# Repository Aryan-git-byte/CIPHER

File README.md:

# CIPHER — Journal Export

- Exported at: 2026-05-15T09:21:32Z
- Project ID: 8
- Entries: 12

## Entry 1
- ID: 206
- Author: TheMudGuy
- Created At: 2026-03-19T09:36:23Z

### Content

# CIPHER
## Compact Integrated Platform for Hardware Engineering and Research

### Objective:
An integrated portable workstation with 8 gigabytes of ram, plenty of storage (target - 256 gb ssd), Exposed GPIO headers(SPI, I2C, UART, etc) to test sensors, components directly. 
The communication protocols of the workstation are LTE, LoRa, WiFi, and BLE.
It will have the following ports:
- 4x USB 3.0 A port
- 1x USB-C for Charging
- 1x USB 3.0 C for Data
- 1x Ethernet Port
- 1x 3.5 mm Audio Jack
- 1x Barrel jack for backup power to power the workstation directly from wall adaptor.
- 1x SD card Slot
- 1x self bouncing Nano SIM card slot
- 1x HDMI port

**For the GPIO pins we will have:**
- GP0 - GP11 : Digital IO/ PWM/ ADC
- I2C(SDA, SCL)
- SPI (MOSI, MISO, SCK, CS)
- 2x 3V3 pin
- 2x GND pin
- 2x 5V pin

## Modularity:

The Cyberdeck will be divided into 1 main board and 5 daughterboards(this number can be changed as we develop further) that will communicate with each other using protocols such as SPI,UART etc.
The main board will have :
- The CM5108000module itself
- And all the ports

**Now the Daughterboards are:**
1. Power Board:
 - it is responsible to lookup for the battery
 - Charging
 - Powering all the components in CIPHER
 - and exposing power outlet on the panel too
 - charge the batteries
 - protect from overcharge & over discharge, implement cell balancing, and obv prevent it from blowing up
 - supply 2  channels of 5v at 6A peak current and 3.3v at 5A peak with low power loss & high efficiency
 - monitor batteries and report it to CM5
 -8 18650 cells @ 2600 mah

2. Instrument Board
 - This board will have the Logic analyzer and a oscilloscope
 - the main mcu of this board will be a Pi pico 2, it will be placed there through female socket, making it replacable
3. GPIO Board
 - This board is responsible to expose the GPIO pins out the laptop
 - The main MCU of this board will be a  Pi pico 2, it will be placed there through female socket, making it replacable
 - It will be programmable through USB, which will be routed inside of the CIPHER
4. Radio Board
 - This will have all the communication modules such as LoRa, LTE, Sim slot, Antenna conectors.
 - This board will be operateed directly by the Main Board
5. Keyboard & Trackpad
 - This board will have a low profile 60-75% keyboard(tbd)
 - and a trackpad
 - The main mcu of this board is a  Pi pico 1, it will also be placed there through female socket, making it replacable

also i m using the devboard instead of IC , cuz using devboard can make it replacable and not waste the whole thing just bcz of a mcu if it blow. and it can also save up SMT cost.
currently i have started working on the power board
here how it went 
firstly i checked some ustom cyberdeck by others and how they are powered, read datasheet of cm5 about how much power it needs to work reliably. then  i searched differnet batteries & cells avaialble , from which i chose 
https://robu.in/product/dmegc-inr18650-26e-3-7v-2600mah-li-ion-battery/#tab-product_download_66939_tab

read the datasheet of that exact batteries, searched reviews, studied abt it, then i started looking for things such as buck converter ics, charging ics, which were pretty hard to find in india so at last i decided to use LCSC.
then i read the datasheets of the following components to be used, and implemented their application in my schematic, and i also implemented battery protection features, and fuel gauge, 
this whole process was too long, from reading datasheets, searching hrs for a single ic to found that it has to be imported, now here are some pics of the schematics that i 've created as of now:

also, i forgot to timelapse this cm5 carrier board work, although its not much so i'll just ignore the hrs of it, it was smthg around 1-2 hrs too, it was mostly taken reefernce from the official cm5 carrier board thats why it was quick

### Recording Links

- https://public.lapse-hackclub.link/timelapses/pCE9Pr_62jN5/timelapse-pCE9Pr_62jN5.mp4

## Entry 2
- ID: 320
- Author: TheMudGuy
- Created At: 2026-03-22T14:30:19Z

### Content

today, first i started by implemting chargin feature in my schematic with ip2368, but i found out that the symbol of this ic didnt existed for kicad, so had to drew it too, and then started implementing it in the board , and overall completed the whole power board except the connectors that are to be placed:

after that i started working on the navigation board which had, a tft, an oled, low profile mx style switches, rotary encoders and a touch panel for trackpad.

the problem that i faced while making the navigation board was that i couldnt find a easy to use modular trackpad or touchpad at first, which i overcame by using this touch panel for evelta:

after that i started working on the breakout board which is still kinda incomplete, i spent most of my time finding the best ICs for integrated power supply, but i realized that even a basic buck and separte boost can do the job, so i did that, and implemented both buck & boost parrallely:

thats all i did  on this day, see yaa

### Recording Links

- https://public.lapse-hackclub.link/timelapses/NV78D3_SI4x4/timelapse-NV78D3_SI4x4.mp4
- https://public.lapse-hackclub.link/timelapses/kjuWi_eqHoEB/timelapse-kjuWi_eqHoEB.mp4
- https://public.lapse-hackclub.link/timelapses/5uAo6Y--3Oyj/timelapse-5uAo6Y--3Oyj.mp4

## Entry 3
- ID: 1218
- Author: TheMudGuy
- Created At: 2026-04-05T07:55:29Z

### Content

hiii, today i started by organizing the CM5 carrier board schematic, which previously looked like a mess is now a clean schematic:

and the changes i did are as follows:
- i replaced stacked USB_A with 1x USB3-A and 1x USB3-C.the takeoff the USB-C is that it will behave as usb3 only one way and when inserted the other way it will behave as a normal USB2.0:

- i also added a USB2.0 hub ic , to connect the navigation board and GPIO breakout board with the CM5 through USB:

- i also replaced 2x HDMI-A with 1x HDMI-A and 1x HDMI-C.:

- and simplified the NVMe port:

after that i started researching about the Monitor to use and selected this one:

this is all the things i did, and as always chosing Display is not easy man, u have to like scroll a lot and then hop on one.

### Recording Links

- https://public.lapse-hackclub.link/timelapses/9NkPjEwhZABB/timelapse-9NkPjEwhZABB.mp4
- https://public.lapse-hackclub.link/timelapses/8x_S-KY60xsu/timelapse-8x_S-KY60xsu.mp4
- https://public.lapse-hackclub.link/timelapses/LRWA-5fO69hY/timelapse-LRWA-5fO69hY.mp4

## Entry 4
- ID: 3183
- Author: TheMudGuy
- Created At: 2026-04-21T10:12:32Z

### Content

Hiiii, so today i decided to complete the schematic of the CIPHER - main board so first  i placed a DAC IC PCM5102A for high quality sound in my CyberDeck and then i connected it along with a headphone jack:

after that i made the connection of the NvMe Slot for the ssd

and after completing this i started working on the ethernet and made its schematic too 

### Recording Links

- https://public.lapse-hackclub.link/timelapses/tmAsFf3opQUc/timelapse-tmAsFf3opQUc.mp4

## Entry 5
- ID: 3184
- Author: TheMudGuy
- Created At: 2026-04-21T10:21:03Z

### Content

Hiiiii, so today i started by arranging my messed up schematic, and i wired the 40 pins header in the main board for future use or if smtimes i need em in case

 by referencing the actual CM5IO Board, so that it is standardized.
after that i completed the SD card schematic and organized it.:

with a power load switch.

after that i added misc. such as leds , missed out labels, headers etc based on the actual CM5IO board and referncing it .

i even put dozens of test points here and there so that i can be safe in the future with my test points if smthg goes wrong 

then i added DSI/CSi connectors in the schematic:

 and after that i organized it in a hierarchial sheet and labelled em and conencted em neatly:

after that i doubled whole main board and ensured everythign is right and connected left out lables or pins.

### Recording Links

- https://public.lapse-hackclub.link/timelapses/-HCTVPgyLOj2/timelapse--HCTVPgyLOj2.mp4

## Entry 6
- ID: 3193
- Author: TheMudGuy
- Created At: 2026-04-21T11:01:51Z

### Content

Hi yall, so i wanted to add LTE to my Cyberdeck, because thats cool, + like i can maybe attend my calls with a cyberdeck too ,and access internet from anywhere. so i started my hunting by searching for some modules and stumbled upon SIM7670-G and sim7600e-h, both of which are very popular options. then i started to dig more about em , and found out that sim7600e-h is superior to the SIM7670-G in terms of download & upload speed.
but also it has some downsides that it is a bit more expensive and it has more current requirement, but its features justify them.
so after that i started looking for its schematic and refernce designs to follow. and imported the symbol to the kicad and placed it.

after that  i started by adding another usb hub in the Schematic bcz my other board were in need of more"

and fighting with wires & neatness in the hierarchial sheet nets.

then i morphed one power supply from 5v to 4.2v then 3.8v for the radio board.then i read its datasheet again and watched some reference designs to connect it.

### Recording Links

- https://public.lapse-hackclub.link/timelapses/MTlOoLgT0HFM/timelapse-MTlOoLgT0HFM.mp4
- https://public.lapse-hackclub.link/timelapses/xy6RJpzRv5JQ/timelapse-xy6RJpzRv5JQ.mp4

## Entry 7
- ID: 3195
- Author: TheMudGuy
- Created At: 2026-04-21T11:05:27Z

### Content

hiii, this time i added some missing components in the schematic and added bunch of testpoints. and tehn i started researching for other modules and radio communications to  have on my deck, and i finalized LoRa as one of them, and i researched bout it added it to schematic and wried it all :

and also i m using this specific LoRa module:

SX1262S915N0S1

### Recording Links

- https://public.lapse-hackclub.link/timelapses/B6GcOzRcl61j/timelapse-B6GcOzRcl61j.mp4

## Entry 8
- ID: 3199
- Author: TheMudGuy
- Created At: 2026-04-21T11:19:14Z

### Content

today, my goal was to complete the whole schematic .
first i polished the main board and then i made the instrument board that consist of  a logic analyzer and an oscilloscope:

this board is connected to the main board through USB data lines.
which will communicate over serial communication to the main board.

### Recording Links

- https://public.lapse-hackclub.link/timelapses/2C-y4Fbgew83/timelapse-2C-y4Fbgew83.mp4

## Entry 9
- ID: 3200
- Author: TheMudGuy
- Created At: 2026-04-21T11:32:17Z

### Content

Hi, today i started by reading ERCs, and trying to fix them. then i started adding connectors in boards, writing its documentations, doing minor changes allover the schematic, sorry i dont remember much bcz im journaling after like 6 days, but i will consistent starting from today.
soo yhh i did all that, start writing documentations 
```
# CIPHER - A Detailed OverView of the Schematic:

This is CIPHER, A Compact Integrated Platform For Hardware & Engineering Research.  
And in this doc i will discuss about the schematic of the CIPHER and how each Module (referred as Daughterboard) will communicate and interact with each other. Also before reading this if u havent read [link](About-CIPHER.md).  
Starting off with the Overall Schematic, in this page i wanted to demonstrate how the Daughter Boards, will be connected to each other through connectors such as JST-XH, JST-SH, WS-90 etc.

# 1 Overall Schematic:

Figure.1:

In the Above Figure showing the Overall Schematic page, we are seeing 6 Hierarchial sheets which are as follows:

1. Main Board
2. Power Board
3. Navigation Board
4. GPIO Breakout Board
5. Instrument Board
6. Radio Board

The Connection between these 6 boards will be implemented in this way:

- Power Board $\to$ Main Board through 2(3.3V, 5V) 01x02 WS-90 Connectors
- Power Board $\to$ Radio Board through 3(3.3V, 3.8V, 5V) 01x02 WS-90 Connectors
- Power Board $\to$ Navigation Board through a 01x02 JST-XH connector for 5V and GND
- Power Board $\to$ GPIO Breakout Board through a 01x03(5V, GND, VBAT) JST-XH connector
- Power Board $\to$ Instrument Board through a 01x02(5V and GND) JST-XH connector

therefore total number of connectors dedicated for power are as follows:

- 5x 01x02 WS-90 Connectors
- 2x 01x02 JST-XH Connectors
- 1x 01x03 JST-XH Connectors

where

- 2x WS-90 for 3.3v rail
- 2x WS-90 for 5v rail
- 1x WS-90 for 3.8v rail
- 1x 01x02 JST-XH for 3.3v rail
- 1x 01x02 JST-XH for 5v rail
- 1x 01x03 JST-XH for VBAT and 5v rail

after completing the power rail , we can move on to the Signals Connectors.

here we'll first encounter the Navigation Board with a 01x04 JST-XH connector having (SCL, SDA, USB_DP, USB_DM) going to CM5 in the same order.

Next we have the GPIO Breakout Board connected to the Main Board through a 01x02 JST-XH Connector in the order (USB_DM, USB_DP) And same for the Instrument Board ASWELL,

and for the Connection between Radio Board and Main Board we will use a 01x08 JST-XH connector in the order (CEO, GPIO5, GPIO22, GPIO17, GPIO17, GPIO27, MOSI, MISO, SCK)

In conclusion:

1. 1x 01x04 JST-XH connector
2. 2x 01x02 JST-XH connector
3. 1x 01x08 JST-XH connector

And now with this he whole Overall Schematic is done connecting all the DaughterBoards with the Main Board.
```

okay so after this i faced a sudden power cut and my all files + a 2 hr recording,, so i was very depressed after this. and stopped working on CIPHER for 1-2 days , then i retur back on 18th april. the main issue was that the files in the git history were too old. and the kicad only had backup of overall schematic, not others  hierarchial sheets,
 so  regarding this i came and undo whatever i had in my git history and with a pdf i saved last time, i started restoring the schematic bit by bit

### Recording Links

- https://public.lapse-hackclub.link/timelapses/ZGyMXbbkUDuW/timelapse-ZGyMXbbkUDuW.mp4
- https://public.lapse-hackclub.link/timelapses/A-Lmj8DnW7kE/timelapse-A-Lmj8DnW7kE.mp4

## Entry 10
- ID: 3201
- Author: TheMudGuy
- Created At: 2026-04-21T11:41:46Z

### Content

Hi today i started again by restoring the schematic and writing the docs of the Schematic connections:
```
# CIPHER - A Detailed OverView of the Schematic:

This is CIPHER, A Compact Integrated Platform For Hardware & Engineering Research.  
And in this doc i will discuss about the schematic of the CIPHER and how each Module (referred as Daughterboard) will communicate and interact with each other. Also before reading this if u havent read [link](About-CIPHER.md).  
Starting off with the Overall Schematic, in this page i wanted to demonstrate how the Daughter Boards, will be connected to each other through connectors such as JST-XH, JST-SH, WS-90 etc.

# 1 Overall Schematic:

Figure.1:

In the Above Figure showing the Overall Schematic page, we are seeing 6 Hierarchial sheets which are as follows:

1. Main Board
2. Power Board
3. Navigation Board
4. GPIO Breakout Board
5. Instrument Board
6. Radio Board

The Connection between these 6 boards will be implemented in this way:

- Power Board $\to$ Main Board through 2(3.3V, 5V) 01x02 WS-90 Connectors
- Power Board $\to$ Radio Board through 3(3.3V, 3.8V, 5V) 01x02 WS-90 Connectors
- Power Board $\to$ Navigation Board through a 01x02 JST-XH connector for 5V and GND
- Power Board $\to$ GPIO Breakout Board through a 01x03(5V, GND, VBAT) JST-XH connector
- Power Board $\to$ Instrument Board through a 01x02(5V and GND) JST-XH connector

therefore total number of connectors dedicated for power are as follows:

- 5x 01x02 WS-90 Connectors
- 2x 01x02 JST-XH Connectors
- 1x 01x03 JST-XH Connectors

where

- 2x WS-90 for 3.3v rail
- 2x WS-90 for 5v rail
- 1x WS-90 for 3.8v rail
- 1x 01x02 JST-XH for 3.3v rail
- 1x 01x02 JST-XH for 5v rail
- 1x 01x03 JST-XH for VBAT and 5v rail

after completing the power rail , we can move on to the Signals Connectors.

here we'll first encounter the Navigation Board with a 01x04 JST-XH connector having (SCL, SDA, USB_DP, USB_DM) going to CM5 in the same order.

Next we have the GPIO Breakout Board connected to the Main Board through a 01x02 JST-XH Connector in the order (USB_DM, USB_DP) And same for the Instrument Board ASWELL,

and for the Connection between Radio Board and Main Board we will use a 01x08 JST-XH connector in the order (CEO, GPIO5, GPIO22, GPIO17, GPIO17, GPIO27, MOSI, MISO, SCK)

In conclusion:

1. 1x 01x04 JST-XH connector
2. 2x 01x02 JST-XH connector
3. 1x 01x08 JST-XH connector

And now with this he whole Overall Schematic is done connecting all the DaughterBoards with the Main Board.

# 2 NAVIGATION BOARD:

Figure.2:

In this Schematic Shown above, We have our 75% Keyboard, A MCU(RP2040), A GPIO Expander, 2 Rotaries with Switches, 1 TouchScreen TFT for Macros, 1 OLED for System Info and 1 Touch Panel For Trackpad.

## Details:

- **SW2 - SW85** Are Switches of the Keyboard forming a Matrix along with **D9 - D92**. Matrix Formed are **R1-R6** and **C1-C16**. where Rs are connected to the A2 (RP Pi Pico) in the following Connection:

| Row No. | Pin No. | Pin Name |
| ------- | ------- | -------- |
| R1      | 4       | GPIO2    |
| R2      | 5       | GPIO3    |
| R3      | 6       | GPIO4    |
| R4      | 7       | GPIO5    |
| R5      | 9       | GPIO6    |
| R6      | 10      | GPIO7    |

And C1-C16 are connected to the U16 (PCA9555D) in the following connections:
|Row No.| Pin No.|Pin Name|
|-------|--------|--------|
| C1 |4|IO0_0|
| C2 |5|IO0_1|
| C3 |6|IO0_2|
| C4 |7|IO0_3|
| C5 |8|IO0_4|
| C5 |9|IO0_5|
| C6 |10|IO0_6|
| C7 |11|IO0_7|
| C8 |13|IO01_0|
| C9 |14|IO01_1|
| C10 |15|IO01_2|
| C11 |16|IO01_3|
| C12 |17|IO01_4|
| C13 |18|IO01_5|
| C14 |19|IO01_6|
| C15 |20|IO01_7|

- Then , We Have SW86 and SW87 which are EC11 connected to the A2 (RP pi pico) in following connections:

| Pin No. Of Rotary Encoders | Pin No. of RP pi pico | Pin Name |
| -------------------------- | --------------------- | -------- |
| SW86_A                     | 32                    | GPIO27   |
| SW86_B                     | 34                    | GPIO28   |
| SW87_A                     | 12                    | GPIO9    |
| SW87_B                     | 14                    | GPIO10   |

and the switch side of these encoders are connected in the matrix in this way:

- SW86_S1 $\to$ C14 net
- SW86_S2 $\to$ R2 net
- SW87_S1 $\to$ C14 net
- SW87_S2 $\to$ R3 net

Next, we Have

- J28 (GME0831B), which is a 5" I2C touch panel whose SDA and SCL are connected directly to the CM5, and Int and RST pin to Pi Pico connected like:
- GME0831B_1 $\to$ P11 of pi pico
- GME0831B_2 $\to$ P12 of pi pico
- GME0831B_4 $\to$ SDA of pi pico
- GME0831B_5 $\to$ SCL of pi pico
  Then we have,
- two displays in which one of them is a 2.8" J25 TFT(used for Macros) and one is 0.96" J26 OLED (used for system info)

| TFT   | Pi pico |
| ----- | ------- |
| CS    | P17     |
| RST   | P21     |
| DC    | P20     |
| MOSI  | P19     |
| SCK   | P18     |
| LED   | P8      |
| MISO  | P16     |
| T_CLK | P18     |
| T_CS  | P26     |
| T_DIN | P19     |
| T_DO  | P16     |
| T_IRQ | P22     |

| OLED | Pi pico |
| ---- | ------- |
| SCL  | P14     |
| SDA  | P15     |

- And at last we have the Mcu A2 & GPIO U15 GPIO expander, Where GPIO expander (PCA9555D), Is connected to the pi pico on pin 14 & 15. using I2C. and pi pico is powered by the 5v lane.

```

and this is the complete schematic as of now:

and after that i started journaling my projects

### Recording Links

- https://public.lapse-hackclub.link/timelapses/LeHkxJ-kFLGI/timelapse-LeHkxJ-kFLGI.mp4
- https://public.lapse-hackclub.link/timelapses/Tcjf3Nbry5ca/timelapse-Tcjf3Nbry5ca.mp4

## Entry 11
- ID: 6212
- Author: TheMudGuy
- Created At: 2026-05-09T05:51:37Z

### Content

Hi, so today i started by importing some symbol to kicad and then changed the buck converter ic in the power board to make it more power-efficient and previous buck converters were overkill so fixed it then i also edited the ic symbol to make it easier to use and designed the whole schematic:

### Recording Links

- https://public.lapse-hackclub.link/timelapses/xkmwdyNnk9PY/timelapse-xkmwdyNnk9PY.mp4

## Entry 12
- ID: 6589
- Author: TheMudGuy
- Created At: 2026-05-11T13:45:11Z

### Content

Today i changed my charging circuitory from those complex IC to simple charging circuit with a barrel jack 

Because I didn't wanted to make the BOM and project anymore complex I stripped down that much complexity and I may strip down even more functionalities for V1 in future.

### Recording Links

- https://public.lapse-hackclub.link/timelapses/vfAe_d3sIZTV/timelapse-vfAe_d3sIZTV.mp4

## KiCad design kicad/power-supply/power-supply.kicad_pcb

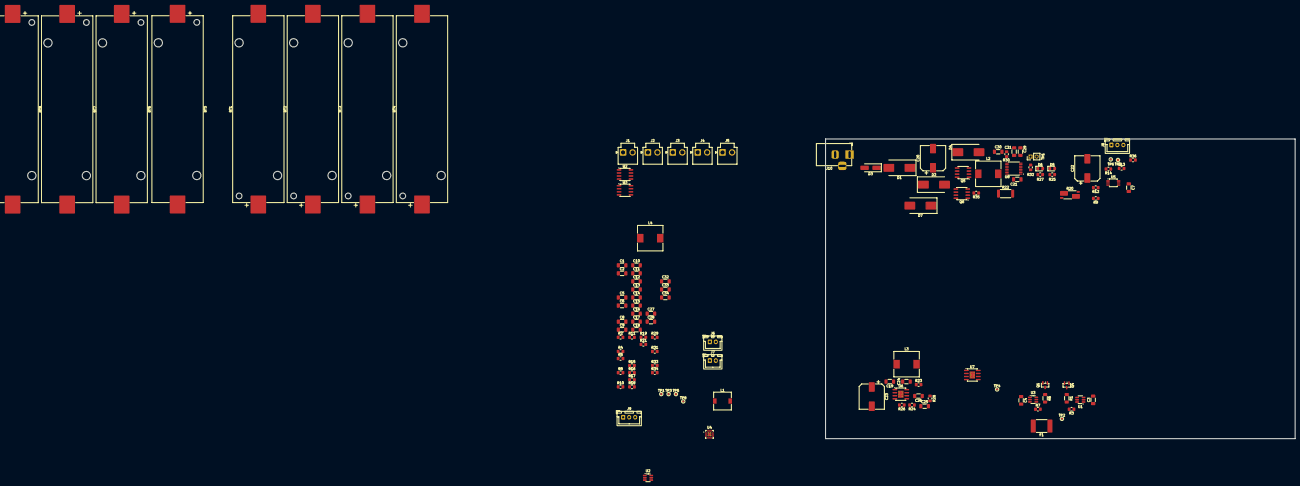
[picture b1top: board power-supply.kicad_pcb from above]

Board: 2 copper layers, 195.5 x 124.8 mm, 123 parts (0 on the bottom side), 68 nets, no tracks yet.

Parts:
BT1, BT2, BT3, BT4, BT5, BT6, BT7, BT8: 18650; BatteryHolder_Keystone_1042_1x18650
C1, C2, C3, C4, C6, C7, C10, C11: 100n; C_1206_3216Metric_Pad1.33x1.80mm_HandSolder
C5: 1u; C_1206_3216Metric_Pad1.33x1.80mm_HandSolder
C8, C9, C12, C13, C14, C15, C16: 22u; C_1206_3216Metric_Pad1.33x1.80mm_HandSolder
C17: 100p; C_1206_3216Metric_Pad1.33x1.80mm_HandSolder
C18: 22n; C_1206_3216Metric_Pad1.33x1.80mm_HandSolder
C19, C27: 10nF; C_1206_3216Metric_Pad1.33x1.80mm_HandSolder
C20, C22: 470uF; CP_Elec_10x10
C21, C31: 100 nF; C_1206_3216Metric_Pad1.33x1.80mm_HandSolder
C23: 10uF/25V; CP_Elec_10x10
C24, C32: 0.1uF; C_1206_3216Metric_Pad1.33x1.80mm_HandSolder
C25, C33: 12uF; C_1206_3216Metric_Pad1.33x1.80mm_HandSolder
C26, C34: 3.9nF; C_1206_3216Metric_Pad1.33x1.80mm_HandSolder
C28: 10uF/25V; C_1206_3216Metric_Pad1.33x1.80mm_HandSolder
C29: 470pF; C_1206_3216Metric_Pad1.33x1.80mm_HandSolder
C30: 220nF; C_1206_3216Metric_Pad1.33x1.80mm_HandSolder
D1, D2, D4: SK54; D_SMC_Handsoldering
D3: SMAJ22A; D_SMA_Handsoldering
D5, D6: LED; LED_0805_2012Metric_Pad1.15x1.40mm_HandSolder
D7: D; D_SMC_Handsoldering
F1: Fuse; Fuse_2920_7451Metric_Pad2.10x5.45mm_HandSolder
J1, J2, J3, J4, J5: Conn_01x02; JST_VH_B2P-VH-B_1x02_P3.96mm_Vertical
J6, J7: Conn_01x02; JST_XH_B2B-XH-A_1x02_P2.50mm_Vertical
J8, J9: Conn_01x03; JST_XH_B3B-XH-A_1x03_P2.50mm_Vertical
J10: Barrel_Jack_Switch; BarrelJack_Horizontal
L1: 2.2uH; L_7.3x7.3_H3.5
L2, L3, L4: 10uH; L_10.4x10.4_H4.8
Q1, Q4: Q_NMOS_GSD; SOT-23
Q2, Q3: Q_NMOS_SGD; SOIC-8_3.9x4.9mm_P1.27mm
Q5, Q6: Q_PMOS_SGD; SOIC-8_3.9x4.9mm_P1.27mm
R1, R6: 47; R_1206_3216Metric_Pad1.30x1.75mm_HandSolder
R2, R4: 330; R_0805_2012Metric_Pad1.20x1.40mm_HandSolder
R3, R7: 100; R_0805_2012Metric_Pad1.20x1.40mm_HandSolder
R5: 2K; R_0805_2012Metric_Pad1.20x1.40mm_HandSolder
R8, R32: 0; R_0805_2012Metric_Pad1.20x1.40mm_HandSolder
R9, R12, R13, R14, R16, R36: 10k; R_0805_2012Metric_Pad1.20x1.40mm_HandSolder
R10: 470k; R_0805_2012Metric_Pad1.20x1.40mm_HandSolder
R11: 90K; R_0805_2012Metric_Pad1.20x1.40mm_HandSolder
R15: 150k; R_0805_2012Metric_Pad1.20x1.40mm_HandSolder
R17: 330k; R_0805_2012Metric_Pad1.20x1.40mm_HandSolder
R18: 20K; R_0805_2012Metric_Pad1.20x1.40mm_HandSolder
R19: 5.1K; R_0805_2012Metric_Pad1.20x1.40mm_HandSolder
R20: R_Shunt; R_Shunt_Vishay_WSK2512_6332Metric_T2.21mm
R21, R23, R29: 100K; R_0805_2012Metric_Pad1.20x1.40mm_HandSolder
R22: 0.05Ω; R_2512_6332Metric
R24: 30.9K; R_0805_2012Metric_Pad1.20x1.40mm_HandSolder
R25, R27: 4.7k; R_0805_2012Metric_Pad1.20x1.40mm_HandSolder
R26, R33: 10K; R_0805_2012Metric_Pad1.20x1.40mm_HandSolder
R28: 6.8K; R_0805_2012Metric_Pad1.20x1.40mm_HandSolder
R30: 120; R_0805_2012Metric_Pad1.20x1.40mm_HandSolder
R31: 26.1K; R_0805_2012Metric_Pad1.20x1.40mm_HandSolder
R34: 6,8K; R_0805_2012Metric_Pad1.20x1.40mm_HandSolder
R35: 100k; R_0805_2012Metric_Pad1.20x1.40mm_HandSolder
TH1: Thermistor_NTC; PinHeader_1x02_P2.54mm_Vertical
TP1, TP2, TP3, TP4, TP5, TP6, TP7, TP8: TestPoint; TestPoint_Pad_D1.0mm
U1, U3: HY2213-BB3A; SOT-23-6_Handsoldering
U2: HY2120; SOT-23-6_Handsoldering
U4: TPS568230RJER; VQFN-20-1EP_3x3mm_P0.45mm_EP1.55x1.55mm_ThermalVias
U5: INA226; VSSOP-10_3x3mm_P0.5mm
U6, U7: MP2307; SOIC-8-1EP_3.9x4.9mm_P1.27mm_EP2.29x3mm_ThermalVias
U8: CN3702; TSSOP-16_4.4x5mm_P0.65mm

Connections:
/12V: C20.1, C21.1, D1.1 (K), D7.2 (A), Q5.5 (D), Q5.6 (DRAIN), Q5.7 (DRAIN), Q5.8 (DRAIN), Q6.4 (G), R25.1, R27.1, R35.2, U8.15 (VCC)
/BAT+: C22.1, F1.2, Q6.1 (S), Q6.2 (SOURCE), Q6.3 (SOURCE), R2.1, R20.1, R22.2, TP1.1, U8.14 (BAT)
/BAT-: BT5.2 (-), BT6.2 (-), BT7.2 (-), BT8.2 (-), C1.1, C2.2, C4.2, Q1.2 (S), Q2.1 (S), Q2.2 (SOURCE), Q2.3 (SOURCE), TP4.1, U2.6 (VSS), U3.3 (VSS)
/BAT_MID: BT1.2 (-), BT2.2 (-), BT3.2 (-), BT4.2 (-), BT5.1 (+), BT6.1 (+), BT7.1 (+), BT8.1 (+), C3.2, Q4.2 (S), R4.1, R6.2, R7.2, U1.3 (VSS)
/GPIO: J8.3, R36.2, U5.3 (~Alert)
/PBS+: C8.1, C9.1, C10.1, C23.1, C28.1, D7.1 (K), J9.3, Q6.5 (D), Q6.6 (DRAIN), Q6.7 (DRAIN), Q6.8 (DRAIN), R10.1, R20.4, R23.2, R29.2, TP8.1, U4.2 (VIN), U4.3 (VIN), U4.4 (VIN), U4.5 (VIN), U6.2 (2_IN), U7.2 (2_IN)
/SCL: J8.2, R13.1, TP7.1, U5.5 (SCL)
/SDA: J8.1, R14.1, R16.1, TP6.1, U5.4 (SDA)
/VCC: C5.2, R17.1, R21.2, U4.17 (VCC)
/VOUT-1: C11.1, C12.1, C13.1, C14.1, C15.1, C16.1, C17.1, J1.1, J4.1, J6.1, J7.1, J9.1, L1.2, R11.1, TP5.1
/VOUT-2: C25.1, J2.1, L3.2, R24.1
/VOUT-3: C7.2, C33.1, J3.1, J5.1, L4.2, R13.2, R14.2, R16.2, R31.1, R36.1, U5.6 (VS)
GND: C5.1, C7.1, C8.2, C9.2, C10.2, C11.2, C12.2, C13.2, C14.2, C15.2, C16.2, C18.2, C20.2, C22.2, C23.2, C24.1, C25.2, C28.2, C29.2, C30.2, C31.2, C32.1, C33.2, D3.2 (A2), D4.2 (A), J1.2, J2.2, J3.2, J4.2, J5.2, J6.2, J7.2, J9.2, J10.2, J10.3, Q3.1 (S), Q3.2 (SOURCE), Q3.3 (SOURCE), R5.1, R9.2, R12.2, R18.2, R19.2, R26.2, R28.1, R32.2, R33.2, R34.1, R35.1, TH1.2, TP3.1, U4.7 (GND), U4.8 (GND), U4.10 (NC), U4.13 (GND), U4.16 (NC), U4.18 (GND), U4.21 (PAD), U5.7 (GND), U6.4 (4_GND), U6.9 (4_GND), U7.4 (4_GND), U7.9 (4_GND), U8.2 (PGND), U8.3 (GND), U8.10 (TEST)
unnamed: BT1.1 (+), BT2.1 (+), BT3.1 (+), BT4.1 (+), F1.1, R1.2, R3.2, TP2.1
unnamed: C6.1, R8.2
unnamed: C6.2, L1.1, U4.6 (SW), U4.19 (SW), U4.20 (SW)
unnamed: C26.1, R28.2
unnamed: C30.1, R30.2
unnamed: C34.1, R34.2
unnamed: D1.2 (A), D3.1 (A1), J10.1
unnamed: D2.2 (A), Q5.1 (S), Q5.2 (SOURCE), Q5.3 (SOURCE)
unnamed: D2.1 (K), D4.1 (K), L2.1
unnamed: D5.2 (A), R25.2
unnamed: D5.1 (K), U8.4 (CHRG)
unnamed: D6.2 (A), R27.2
unnamed: D6.1 (K), U8.5 (DONE)
unnamed: Q1.3 (D), R6.1
unnamed: Q1.1 (G), U3.6 (OUT)
unnamed: Q2.5 (D), Q2.6 (DRAIN), Q2.7 (DRAIN), Q2.8 (DRAIN), Q3.5 (D), Q3.6 (DRAIN), Q3.7 (DRAIN), Q3.8 (DRAIN)
unnamed: Q2.4 (G), U2.1 (OD)
unnamed: Q3.4 (G), U2.2 (OC)
unnamed: Q4.3 (D), R1.1
unnamed: Q4.1 (G), U1.6 (OUT)
unnamed: Q5.4 (G), U8.16 (DRV)
unnamed: C3.1, R3.1, U1.2 (VDD)
unnamed: R5.2, U2.3 (CS)
unnamed: C2.1, R4.2, U2.4 (VC)
unnamed: C1.2, R2.2, U2.5 (VDD)
unnamed: C4.1, R7.1, U3.2 (VDD)
unnamed: R8.1, U4.1 (BST)
unnamed: R10.2, R15.2, U4.12 (EN)
unnamed: C17.2, R11.2, R18.1, U4.14 (FB)
unnamed: R17.2, R19.1, U4.15 (MODE)
unnamed: R21.1, U4.9 (PGOOD)
unnamed: C18.1, U4.11 (SS)
unnamed: R12.1, U5.2 (A0)
unnamed: R9.1, U5.1 (A1)
unnamed: R20.3, U5.8 (Vbus), U5.9 (Vin-)
unnamed: R20.2, U5.10 (Vin+)
unnamed: C19.1, U6.1 (1_BS)
unnamed: C19.2, L3.1, U6.3 (3_SW)
unnamed: R24.2, R26.1, U6.5 (5_FB)
unnamed: C26.2, U6.6 (6_COMP)
unnamed: R23.1, U6.7 (7_EN)
unnamed: C24.2, U6.8 (8_SS)
unnamed: C27.1, U7.1 (1_BS)
unnamed: C27.2, L4.1, U7.3 (3_SW)
unnamed: R31.2, R33.1, U7.5 (5_FB)
unnamed: C34.2, U7.6 (6_COMP)
unnamed: R29.1, U7.7 (7_EN)
unnamed: C32.2, U7.8 (8_SS)
unnamed: C29.1, U8.8 (COM1)
unnamed: R30.1, U8.9 (COM2)
unnamed: C31.1, U8.11 (COM3)
unnamed: L2.2, R22.1, U8.13 (CSP)
unnamed: R32.1, U8.7 (EOC)
unnamed: TH1.1, U8.6 (TEMP)
unnamed: C21.2, U8.1 (VG)

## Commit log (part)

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2026-03-18 git init
2026-03-20 completed power board
2026-03-20 completed the navigation board schematic
2026-03-20 update gpiio board
2026-04-01 made overall schematic
2026-04-01 worked on main board
2026-04-05 worke don the usb hub
2026-04-09 updated the main board, changes journaled in the fallout journaling
2026-04-09 updated the main board
2026-04-10 Completed the main board schematic
2026-04-15 finally completed the schematic
2026-04-18 all data got corrupted bruhh. now , commiting whats left healthy
2026-04-19 DOCUMENTED Till the Navigation board
2026-05-06 changed buck converters
2026-05-15 Initialize README with project details and entries
    Added detailed project documentation and entries for the CIPHER journal, including schematic overview and component descriptions.
2026-06-10 migrating kicad 9 to 10
2026-06-19 Rename README.md to JOURNAL.md
2026-06-19 Revise JOURNAL.md with metadata and new entries
    Updated the journal format to include metadata and improved organization of entries. Added new content and timelapse links for various project updates.
2026-06-19 Enhance formatting and emphasis in JOURNAL.md
    Updated formatting for headings and emphasized key sections in the journal.
2026-06-27 upddate
